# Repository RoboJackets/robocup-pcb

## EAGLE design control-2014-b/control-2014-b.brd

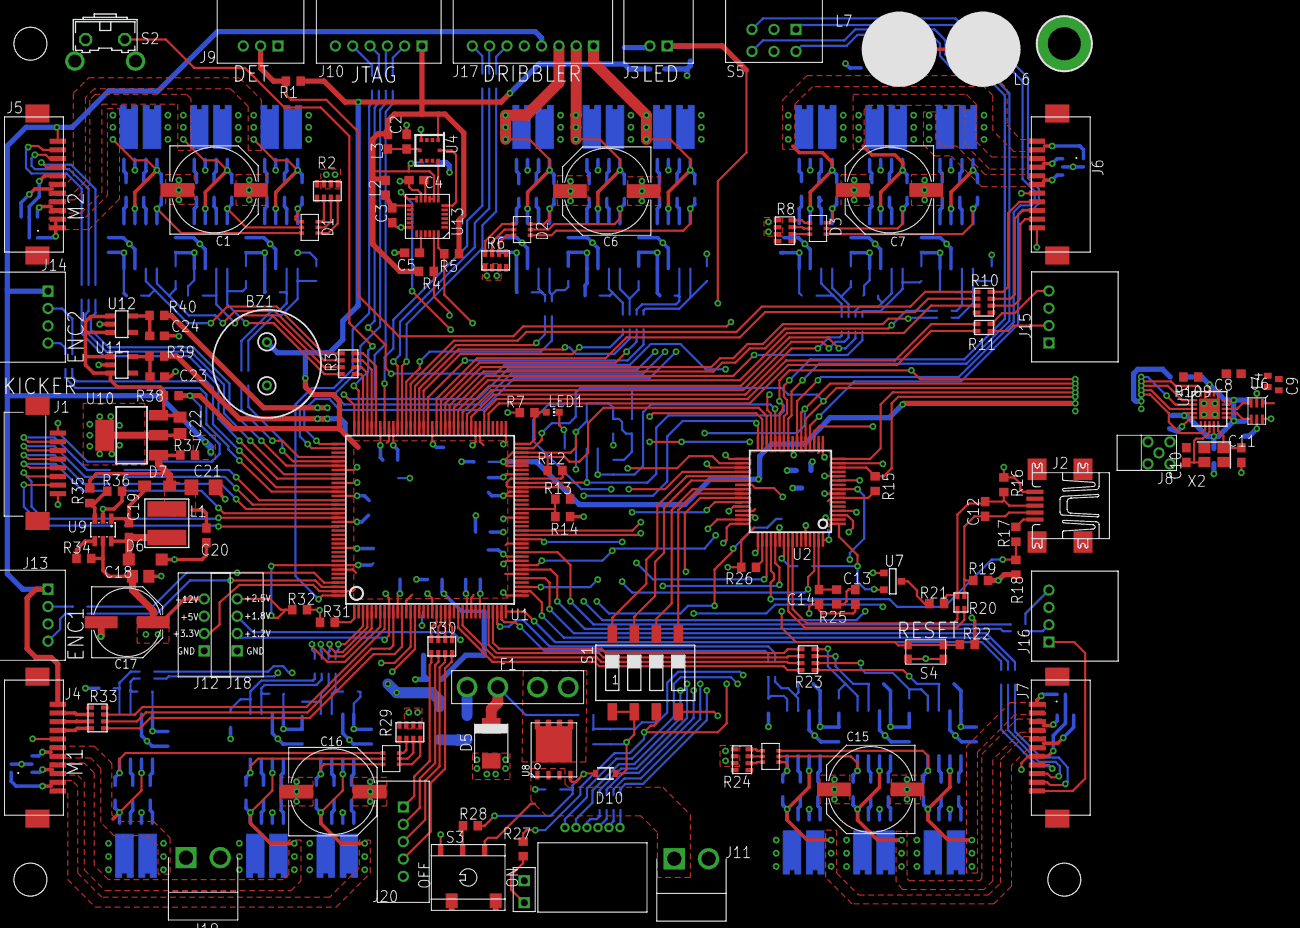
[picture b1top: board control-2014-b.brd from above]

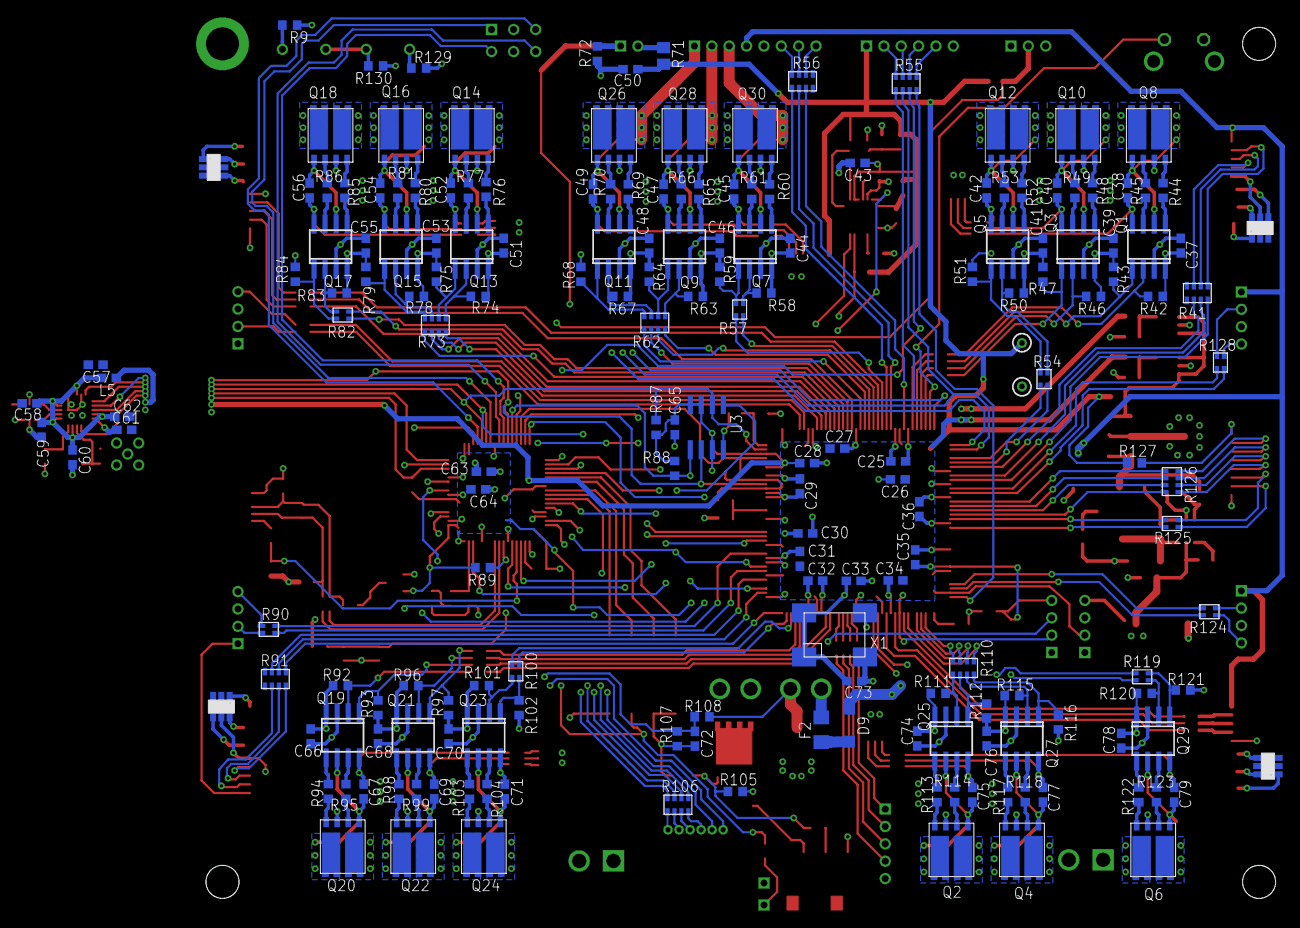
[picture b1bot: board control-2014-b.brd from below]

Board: 4 copper layers, 307 parts (184 on the bottom side), 336 nets.

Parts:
BZ1: PS12
C1, C6, C7, C15, C16: 470uF 25V; PANASONIC_G
C2, C3, C4, C20, C25, C26, C27, C28, C29, C30, C31, C32, C33, C34, C35, C36, C37, C39, C41, C43, C44, C46, C48, C51, C53, C55, C58, C61, C63, C64, C65, C66, C68, C70, C72, C73, C74, C76, C78: 100nF; C0603
C5, C59: 2.2nF; C0603
C8: 100pF; C0603
C9: 500R07S1R8BV4T; C0402
C10, C11: 27pF; C0603
C12: 33pF; C0603
C13, C19, C60, C62: 10nF; C0603
C14: 1nF; C0603
C17: 100uF 25V; PANASONIC_E
C18: 1uF 35V; C0805
C21: 22uF 6.3V; C1206
C22: 10uF; C0805
C23, C24, C50: 1uF; C0603
C38, C40, C42, C45, C47, C49, C52, C54, C56, C67, C69, C71, C75, C77, C79: 47nF; C0603
C57: 220nF; C0603
D1, D2, D3, D4, D8: MMBD4448HTW
D5: SMBJP6KE18A-TP; SMBJ
D6, D9: MBRX160-TP; SOD123
D7: BAS16H; SOD323-W
D10: CDSOD323-T15SC; SOD-323
F1: 2x BK6011 [30A]; FUSE_MINI_ATC
F2: SF-1206F100-2; F1206
H1: MOUNTING_HOLE
J1: 0528520870
J2: MINI-USB; UX60A-MB-5ST
J3: 2MM-2H; 2MM-2-H
J4, J5, J6, J7: Molex 0522711179; FH_11_HOR
J8: MMCX_RA
J9: 2MM-3H; 2MM-3-H
J10: 2MM-6H; 2MM-6-H
J11: BATT; JST_VH_2_RA
J12, J18: 2MM-4V; 2MM-4-V
J13, J14, J15, J16: 2MM-4H; 2MM-4-H
J17: 2MM-8H; 2MM-8-H
J19: JST_VH_2; JST_VH_2_RA
J20: 2MM-5V; 2MM-5-V
L1: SDR0403-270KL; SDR0403
L2, L3, L5: HZ0603B102R-10; C0603
L4: L-07C5N6SV6T; R0402
L6, L7: RL1014
LED1: CHIP-LED0603
LED2: LED2; 5350T5
LED3: LDS-M514RI-RA
Q1, Q3, Q5, Q7, Q9, Q11, Q13, Q15, Q17, Q19, Q21, Q23, Q25, Q27, Q29: FAN7380; SO08
Q2, Q4, Q6, Q8, Q10, Q12, Q14, Q16, Q18, Q20, Q22, Q24, Q26, Q28, Q30: BSC072N03LD
R1: 5.6k; R0603
R2, R6, R8, R24, R29: 22; RA_4_1206
R3, R10, R23, R30, R33, R41, R55, R56, R62, R73, R91, R106, R110, R126: 220; RA_4_1206
R4, R5, R14, R15, R18, R22, R32, R34, R36, R42, R43, R46, R47, R50, R51, R58, R59, R63, R64, R67, R68, R74, R75, R78, R79, R83, R84, R87, R88, R92, R93, R96, R97, R101, R102, R107, R111, R112, R115, R116, R120, R121: 10.0k; R0603
R7, R17, R27, R31: 220; R0603
R9, R129, R130: 10K; R0603
R11, R54, R57, R82, R90, R100, R119, R124, R125, R128: 220; RA_2_0606
R12, R13, R26, R89: NP; R0603
R16, R19: 330k; R0603
R20: 27; RA_2_0606
R21, R25: 1.5k; R0603
R28: 10; R0603
R35: 52.3k; R0603
R37, R38, R39, R40, R127: 0; R0603
R44, R45, R48, R49, R52, R53, R60, R61, R65, R66, R69, R70, R76, R77, R80, R81, R85, R86, R94, R95, R98, R99, R103, R104, R113, R114, R117, R118, R122, R123: 22; R0603
R71: 150 1/8W; R0805
R72, R105: 100k; R0603
R108: 68k; R0603
R109: 56k; R0603
S1: SWS004; SMS-004
S2: B3F-31XX
S3: G3T12AP_SPDT; G3T12AP_SP
S4: KMR2
S5: 94HBB16RAT; HEX-RA-2C
U1: XC3S100E; TQFP144
U2: AT91SAM7S256; SQFP-S-10X10-64
U3: M25P10; SO08
U4: KXTF9-2050; KXTF9
U5: CC1101; QLP20
U6: 0896BM15A0001
U7: FDV304P; SOT-23
U8: SI7141DP; POWERPAK_SO-8
U9: LM2734; SOT23-6L
U10: MCP1824ST-3302E/DB; SOT223
U11: MCP1824T-1202E/OT; SOT23-5
U12: MCP1824T-2502E/OT; SOT23-5
U13: IMU3000
U$25, U$27, U$28, U$29: SMS05T1; SC-74
X1: 18.432MHz; XTAL_LCC
X2: 644-1055-1-ND; XTAL-3.2X2.5

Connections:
12V_LOGIC: C17.+, C18.1, D9.C, J12.4, R34.2, U9.5
+1.2V: C26.1, C27.1, C31.1, C34.1, J18.2, R39.1, U1.9, U1.45, U1.80, U1.115
+1.8V: C64.1, J18.3, U2.8, U2.12, U2.24, U2.54, U2.64
+2.5V: C25.1, C29.1, C32.1, C35.1, J18.4, R7.1, R32.1, R40.1, U1.30, U1.65, U1.102, U1.137
+3.3V: BZ1.2, C28.1, C30.1, C33.1, C36.1, C43.1, C50.1, C63.1, C65.1, C73.1, J10.1, J12.2, L2.1, L3.1, L5.1, R1.1, R4.2, R5.2, R12.2, R13.2, R15.2, R22.2, R26.2, R27.2, R38.2, R71.1, R87.2, R88.2, R89.2, R127.1, S1.3, U1.13, U1.28, U1.42, U1.49, U1.62, U1.64, U1.67, U1.68, U1.70, U1.79, U1.100, U1.121, U1.138, U1.143, U2.1, U2.7, U2.18, U2.45, U2.58, U2.59, U3.3, U3.7, U3.8, U4.1, U7.2, U13.8, U13.9, X1.1, X1.4
+5V: J4.11, J5.11, J6.11, J7.11, J12.3, J13.1, J14.1, J15.1, J16.1, J17.4, R37.2
+12V: C1.+, C6.+, C7.+, C15.+, C16.+, C37.1, C39.1, C41.1, C44.1, C46.1, C48.1, C51.1, C53.1, C55.1, C66.1, C68.1, C70.1, C74.1, C76.1, C78.1, D5.C, F1.3, F1.4, F2.1, J19.1, Q1.3, Q2.D1@1, Q2.D1@2, Q3.3, Q4.D1@1, Q4.D1@2, Q5.3, Q6.D1@1, Q6.D1@2, Q7.3, Q8.D1@1, Q8.D1@2, Q9.3, Q10.D1@1, Q10.D1@2, Q11.3, Q12.D1@1, Q12.D1@2, Q13.3, Q14.D1@1, Q14.D1@2, Q15.3, Q16.D1@1, Q16.D1@2, Q17.3, Q18.D1@1, Q18.D1@2, Q19.3, Q20.D1@1, Q20.D1@2, Q21.3, Q22.D1@1, Q22.D1@2, Q23.3, Q24.D1@1, Q24.D1@2, Q25.3, Q26.D1@1, Q26.D1@2, Q27.3, Q28.D1@1, Q28.D1@2, Q29.3, Q30.D1@1, Q30.D1@2, R2.4, R2.6, R2.8, R6.4, R6.6, R6.8, R8.4, R8.6, R8.8, R24.4, R24.6, R24.8, R29.4, R29.6, R29.8, R108.2
/CONNECT: U2.19, U7.3
ARM_TDI: U1.109, U2.33
ARM_TDO: R55.5, U2.49
BALL_DET: J9.2, R1.2, U2.3
BALL_LED: J3.1, R72.1, U2.44
BATT_SENSE: C72.1, R107.2, R108.1, U2.4
BUZZ: BZ1.1, U2.32
CHASSIS: H1.GND, L6.P$1, R9.1
DDM: R20.2, U2.56
DDP: R20.4, U2.57
DISCHARGE: S2.1, U1.107
DONE: LED1.A, R7.2, U1.72
DP1: S1.8, U2.37
DP2: S1.7, U2.38
DP4: S1.5, U2.41
FLASH_NCS: R88.1, U1.39, U2.28, U3.1
FPGA_NCS: R12.1, U1.69, U2.30
FPGA_SPARE_0: R30.2, U1.20
FPGA_SPARE_1: R30.4, U1.21
FPGA_SPARE_2: R30.6, U1.22
FPGA_SPARE_3: R30.8, U1.23
FPGA_TDI: R55.7, U1.144
FS0: U1.52, U2.31
FS1: U1.51, U2.29
GND: C1.-, C2.2, C3.2, C4.2, C5.2, C6.-, C7.-, C9.2, C10.2, C11.2, C13.2, C14.2, C15.-, C16.-, C17.-, C18.2, C20.2, C21.2, C22.2, C23.2, C24.2, C25.2, C26.2, C27.2, C28.2, C29.2, C30.2, C31.2, C32.2, C33.2, C34.2, C35.2, C36.2, C37.2, C39.2, C41.2, C43.2, C44.2, C46.2, C48.2, C50.2, C51.2, C53.2, C55.2, C57.2, C58.2, C59.2, C60.2, C61.2, C62.2, C63.2, C64.2, C65.2, C66.2, C68.2, C70.2, C72.2, C73.2, C74.2, C76.2, C78.2, D5.A, D6.A, D10.1, J1.8, J2.5, J4.7, J5.7, J6.7, J7.7, J8.P$2, J8.P$3, J8.P$4, J8.P$5, J9.1, J9.3, J10.6, J11.2, J12.1, J13.3, J14.3, J15.3, J16.3, J17.5, J18.1, J19.2, J20.5, LED1.C, LED2.CATHODE, Q1.4, Q2.S2, Q3.4, Q4.S2, Q5.4, Q6.S2, Q7.4, Q8.S2, Q9.4, Q10.S2, Q11.4, Q12.S2, Q13.4, Q14.S2, Q15.4, Q16.S2, Q17.4, Q18.S2, Q19.4, Q20.S2, Q21.4, Q22.S2, Q23.4, Q24.S2, Q25.4, Q26.S2, Q27.4, Q28.S2, Q29.4, Q30.S2, R9.2, R14.1, R16.1, R18.1, R19.1, R36.1, R42.1, R43.1, R46.1, R47.1, R50.1, R51.1, R58.1, R59.1, R63.1, R64.1, R67.1, R68.1, R72.2, R74.1, R75.1, R78.1, R79.1, R83.1, R84.1, R92.1, R93.1, R96.1, R97.1, R101.1, R102.1, R107.1, R109.1, R111.1, R112.1, R115.1, R116.1, R120.1, R121.1, R129.2, R130.1, S1.1, S1.2, S1.4, S2.2, S3.6, S4.1, S4.3, S5.C1, S5.C2, U1.11, U1.19, U1.27, U1.37, U1.46, U1.55, U1.60, U1.61, U1.73, U1.90, U1.99, U1.118, U1.127, U1.133, U2.2, U2.17, U2.46, U2.60, U3.4, U4.4, U5.16, U5.19, U5.DAP, U6.2, U6.5, U6.6, U9.2, U10.2, U10.4, U11.2, U12.2, U13.11, U13.18, U$25.2, U$25.5, U$27.2, U$27.5, U$28.2, U$28.5, U$29.2, U$29.5, X1.2
I2C_SCL: R4.1, U2.36, U13.23
I2C_SDA: R5.1, U2.43, U13.24
ID0: S5.1, U2.23
ID1: S5.2, U2.25
ID2: S5.4, U2.20
ID3: S5.8, U2.26
IMU_INT: U2.34, U13.12
KCHARGE: R126.2, U1.125
KCHIP: R125.3, U1.128
KDONE: R126.4, U1.124
KKICK: R125.1, U1.126
KSCL: R126.6, U1.123
KSDA: R126.8, U1.122
LED_AE: R106.8, U2.35
LED_AN1: LED3.1, U2.9
LED_AN2: LED3.2, U2.42
LED_BF: R106.6, U2.15
LED_CG: R106.4, U2.47
LED_DDP: R106.2, U2.48
M1A: C75.2, J4.1, J4.2, Q2.D2@1, Q2.D2@2, Q2.S1, Q25.6, U$25.1
M1A_H: R110.7, U1.3
M1A_L: R110.5, U1.4
M1B: C77.2, J4.3, J4.4, Q4.D2@1, Q4.D2@2, Q4.S1, Q27.6, U$25.6
M1B_H: R110.3, U1.5
M1B_L: R110.1, U1.7
M1C: C79.2, J4.5, J4.6, Q6.D2@1, Q6.D2@2, Q6.S1, Q29.6, U$25.4
M1C_H: R119.3, U1.14
M1C_L: R119.1, U1.15
M1ENC_A: R124.1, U1.141
M1ENC_B: R124.3, U1.142
M1HALL_A: R33.3, U1.10
M1HALL_B: R33.1, U1.12
M1HALL_C: R33.5, U1.8
M2: R13.1, R14.2, U1.57
M2A: C38.2, J5.1, J5.2, Q1.6, Q8.D2@1, Q8.D2@2, Q8.S1, U$27.1
M2A_H: R3.7, U1.103
M2A_L: R3.5, U1.104
M2B: C40.2, J5.3, J5.4, Q3.6, Q10.D2@1, Q10.D2@2, Q10.S1, U$27.6
M2B_H: R3.3, U1.105
M2B_L: R3.1, U1.106
M2C: C42.2, J5.5, J5.6, Q5.6, Q12.D2@1, Q12.D2@2, Q12.S1, U$27.4
M2C_H: R54.3, U1.112
M2C_L: R54.1, U1.113
M2ENC_A: R128.1, U1.119
M2ENC_B: R128.3, U1.120
M2HALL_A: R41.5, U1.116
M2HALL_B: R41.3, U1.114
M2HALL_C: R41.7, U1.117
M3A: C52.2, J6.1, J6.2, Q13.6, Q14.D2@1, Q14.D2@2, Q14.S1, U$28.1
M3A_H: R73.7, U1.81
M3A_L: R73.5, U1.82
M3B: C54.2, J6.3, J6.4, Q15.6, Q16.D2@1, Q16.D2@2, Q16.S1, U$28.6
M3B_H: R73.3, U1.83
M3B_L: R73.1, U1.85
M3C: C56.2, J6.5, J6.6, Q17.6, Q18.D2@1, Q18.D2@2, Q18.S1, U$28.4
M3C_H: R82.3, U1.86
M3C_L: R82.1, U1.87
M3ENC_A: R11.2, U1.77
M3ENC_B: R11.4, U1.78
M3HALL_A: R10.3, U1.89
M3HALL_B: R10.1, U1.95
M3HALL_C: R10.5, U1.84
M4A: C67.2, J7.1, J7.2, Q19.6, Q20.D2@1, Q20.D2@2, Q20.S1, U$29.1
M4A_H: R23.7, U1.25
M4A_L: R23.5, U1.26
M4B: C69.2, J7.3, J7.4, Q21.6, Q22.D2@1, Q22.D2@2, Q22.S1, U$29.6
M4B_H: R23.3, U1.32
M4B_L: R23.1, U1.33
M4C: C71.2, J7.5, J7.6, Q23.6, Q24.D2@1, Q24.D2@2, Q24.S1, U$29.4
M4C_H: R100.3, U1.34
M4C_L: R100.1, U1.35
M4ENC_A: R90.1, U1.43
M4ENC_B: R90.3, U1.47
M4HALL_A: R91.3, U1.38
M4HALL_B: R91.1, U1.36
M4HALL_C: R91.5, U1.41
M5A: C49.2, J17.1, Q11.6, Q26.D2@1, Q26.D2@2, Q26.S1
M5A_H: R62.3, U1.88
M5A_L: R62.1, U1.91
M5B: C47.2, J17.2, Q9.6, Q28.D2@1, Q28.D2@2, Q28.S1
M5B_H: R62.7, U1.92
M5B_L: R62.5, U1.93
M5C: C45.2, J17.3, Q7.6, Q30.D2@1, Q30.D2@2, Q30.S1
M5C_H: R57.3, U1.94
M5C_L: R57.1, U1.96
M5HALL_A: R56.1, U1.97
M5HALL_B: R56.3, U1.98
M5HALL_C: R56.5, U1.101
MCU_PROGB: R31.1, R32.2, U2.11
MISO: U1.63, U2.27, U3.2, U5.2
MOSI: U1.44, U2.22, U3.5, U5.20
unnamed: J13.4, R124.4
unnamed: J10.3, R55.4
unnamed: Q25.2, R110.8, R111.2
unnamed: J10.5, R55.8
unnamed: Q25.7, R114.1
unnamed: Q2.G1, R114.2
unnamed: Q25.5, R113.1
unnamed: LED3.6, R106.1
unnamed: LED3.5, R106.3
unnamed: LED3.4, R106.5
unnamed: C20.1, C21.1, D7.A, L1.2, R35.2, R37.1, U10.1
unnamed: LED3.3, R106.7
unnamed: LED2.ANODE, R27.1
unnamed: Q2.G2, R113.2
unnamed: Q25.1, R110.6, R112.2
unnamed: Q27.2, R110.4, R115.2
unnamed: Q27.7, R118.1
unnamed: Q4.G1, R118.2
unnamed: Q27.5, R117.1
unnamed: D8.A2, R29.5
unnamed: Q4.G2, R117.2
unnamed: Q27.1, R110.2, R116.2
unnamed: Q29.2, R119.4, R120.2
unnamed: Q29.7, R123.1
unnamed: Q6.G1, R123.2
unnamed: Q29.5, R122.1
unnamed: Q6.G2, R122.2
unnamed: Q29.1, R119.2, R121.2
unnamed: C75.1, D8.C1, Q25.8
unnamed: C77.1, D8.C2, Q27.8
unnamed: C79.1, D8.C3, Q29.8
unnamed: D8.A1, R29.7
unnamed: D8.A3, R29.3
unnamed: Q1.2, R3.8, R42.2
unnamed: Q1.7, R45.1
unnamed: D1.A2, R2.5
unnamed: Q8.G1, R45.2
unnamed: Q1.5, R44.1
unnamed: Q8.G2, R44.2
unnamed: Q1.1, R3.6, R43.2
unnamed: Q3.2, R3.4, R46.2
unnamed: Q3.7, R49.1
unnamed: Q10.G1, R49.2
unnamed: Q3.5, R48.1
unnamed: Q10.G2, R48.2
unnamed: Q3.1, R3.2, R47.2
unnamed: Q5.2, R50.2, R54.4
unnamed: Q5.7, R53.1
unnamed: Q12.G1, R53.2
unnamed: Q5.5, R52.1
unnamed: Q12.G2, R52.2
unnamed: Q5.1, R51.2, R54.2
unnamed: C38.1, D1.C1, Q1.8
unnamed: C40.1, D1.C2, Q3.8
unnamed: C42.1, D1.C3, Q5.8
unnamed: D1.A1, R2.7
unnamed: D1.A3, R2.3
unnamed: Q13.2, R73.8, R74.2
unnamed: Q13.7, R77.1
unnamed: D3.A2, R8.5
unnamed: C22.1, R38.1, U10.3, U11.1, U11.3, U12.1, U12.3
unnamed: Q14.G1, R77.2
unnamed: Q13.5, R76.1
unnamed: Q14.G2, R76.2
unnamed: J3.2, R71.2
unnamed: Q13.1, R73.6, R75.2
unnamed: Q15.2, R73.4, R78.2
unnamed: Q15.7, R81.1
unnamed: C19.2, D6.C, L1.1, U9.6
unnamed: J4.8, R33.2
unnamed: Q16.G1, R81.2
unnamed: J4.10, R33.6
unnamed: Q15.5, R80.1
unnamed: Q16.G2, R80.2
unnamed: J4.9, R33.4
unnamed: J5.8, R41.4
unnamed: J5.10, R41.8
unnamed: J5.9, R41.6
unnamed: J6.8, R10.2
unnamed: J6.10, R10.6
unnamed: J6.9, R10.4
unnamed: J7.8, R91.2
unnamed: J7.10, R91.6
unnamed: C2.1, L3.2, U4.5
unnamed: J7.9, R91.4
unnamed: J17.6, R56.2
unnamed: J17.7, R56.4
unnamed: J1.2, R126.7
unnamed: C23.1, R39.2, U11.5
unnamed: C24.1, R40.2, U12.5
unnamed: R26.1, U2.50
unnamed: C12.2, J2.2, R19.2, R20.1
unnamed: J17.8, R56.6
unnamed: F1.1, F1.2, U8.D@1, U8.D@2, U8.D@3, U8.D@4
unnamed: Q15.1, R73.2, R79.2
unnamed: Q17.2, R82.4, R83.2
unnamed: J1.3, R126.5
unnamed: J1.4, R126.3
unnamed: R34.1, U9.4
unnamed: Q17.7, R86.1
unnamed: U4.9, U13.7
unnamed: C19.1, D7.C, U9.1
unnamed: Q18.G1, R86.2
unnamed: J1.5, R126.1
unnamed: R35.1, R36.2, U9.3
unnamed: J10.4, R55.6
unnamed: R89.1, U2.55
unnamed: J10.2, R55.2
unnamed: C12.1, J2.3, R16.2, R20.3, R21.1
unnamed: R21.2, U7.1
unnamed: C13.1, R25.1
unnamed: C14.1, R25.2, U2.63
unnamed: Q17.5, R85.1
unnamed: D9.A, F2.2
unnamed: Q18.G2, R85.2
unnamed: Q17.1, R82.2, R84.2
unnamed: J13.2, R124.2
unnamed: J16.4, R90.4
unnamed: J16.2, R90.2
unnamed: J15.4, R11.3
unnamed: J15.2, R11.1
unnamed: J14.4, R128.4
unnamed: J14.2, R128.2
unnamed: C52.1, D3.C1, Q13.8
unnamed: U4.10, U13.6
unnamed: C3.1, L2.2, U13.13
unnamed: C4.1, U13.10
unnamed: C5.1, U13.20
unnamed: J1.6, R125.2
unnamed: J1.7, R125.4
unnamed: J1.1, R127.2
unnamed: C61.1, U5.5
unnamed: R109.2, U5.17
unnamed: C11.1, U5.10, X2.1
unnamed: J20.3, R30.5
unnamed: J20.2, R30.3
unnamed: J20.1, R30.1
unnamed: J20.4, R30.7
unnamed: C10.1, U5.8, X2.3
unnamed: C54.1, D3.C2, Q15.8
unnamed: L4.1, U6.1
unnamed: C56.1, D3.C3, Q17.8
unnamed: C8.1, C9.1, L4.2
unnamed: J2.1, R17.2
unnamed: U5.12, U6.4
unnamed: D3.A1, R8.7
unnamed: D3.A3, R8.3
unnamed: Q19.2, R23.8, R92.2
unnamed: Q19.7, R95.1
unnamed: D4.A2, R24.5
unnamed: Q20.G1, R95.2
unnamed: Q19.5, R94.1
unnamed: Q20.G2, R94.2
unnamed: Q19.1, R23.6, R93.2
unnamed: Q21.2, R23.4, R96.2
unnamed: Q21.7, R99.1
unnamed: Q22.G1, R99.2
unnamed: Q21.5, R98.1
unnamed: Q22.G2, R98.2
unnamed: Q21.1, R23.2, R97.2
unnamed: Q23.2, R100.4, R101.2
unnamed: Q23.7, R104.1
unnamed: Q24.G1, R104.2
unnamed: Q23.5, R103.1
unnamed: Q24.G2, R103.2
unnamed: Q23.1, R100.2, R102.2
unnamed: C67.1, D4.C1, Q19.8
unnamed: C69.1, D4.C2, Q21.8
unnamed: C71.1, D4.C3, Q23.8
unnamed: D4.A1, R24.7
unnamed: D4.A3, R24.3
unnamed: U5.13, U6.3
unnamed: C8.2, J8.P$1
unnamed: Q11.2, R62.4, R67.2
unnamed: Q11.7, R70.1
unnamed: D2.A2, R6.5
unnamed: Q26.G1, R70.2
unnamed: Q11.5, R69.1
unnamed: Q26.G2, R69.2
unnamed: Q11.1, R62.2, R68.2
unnamed: Q9.2, R62.8, R63.2
unnamed: Q9.7, R66.1
unnamed: Q28.G1, R66.2
unnamed: Q9.5, R65.1
unnamed: Q28.G2, R65.2
unnamed: Q9.1, R62.6, R64.2
unnamed: Q7.2, R57.4, R58.2
unnamed: Q7.7, R61.1
unnamed: Q30.G1, R61.2
unnamed: Q7.5, R60.1
unnamed: Q30.G2, R60.2
unnamed: Q7.1, R57.2, R59.2
unnamed: C49.1, D2.C3, Q11.8
unnamed: C47.1, D2.C2, Q9.8
unnamed: C45.1, D2.C1, Q7.8
unnamed: D2.A1, R6.7
unnamed: D2.A3, R6.3
unnamed: R28.1, S3.5
unnamed: D10.2, R28.2, R105.1, U8.4
unnamed: L6.P$2, L7.P$1, R130.2
unnamed: L7.P$2, R129.1
PROGB: R31.2, U1.1
RADIO_INT: U2.16, U5.3
RADIO_NCS: R15.1, U2.14, U5.7
RADIO_VDD: C57.1, C58.1, C59.1, C60.1, C62.1, L5.2, U5.4, U5.9, U5.11, U5.14, U5.15, U5.18
SCK: R87.1, U1.71, U2.21, U3.6, U5.1
SRST: R22.1, S4.2, S4.4, U2.39
SYSCLK: U1.50, U2.62, X1.3
TCK: R55.3, U1.110, U2.53
TMS: R55.1, U1.108, U2.51
TST: S1.6, U2.40
VBATT: J11.1, R105.2, S3.4, U8.S@1, U8.S@2, U8.S@3
VBUS: R17.1, R18.2, U2.52

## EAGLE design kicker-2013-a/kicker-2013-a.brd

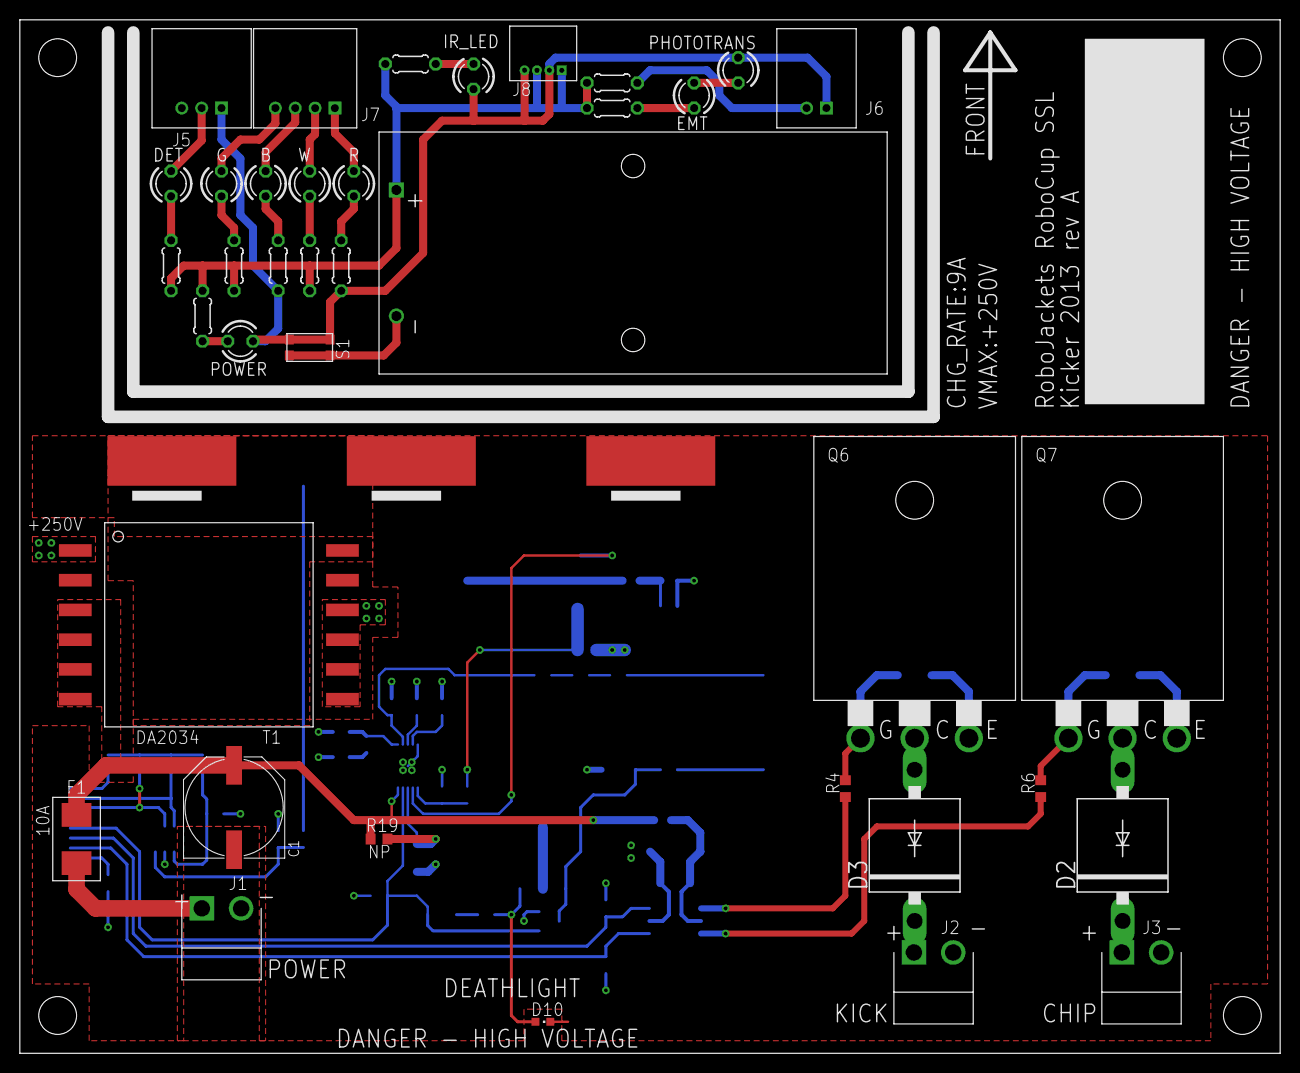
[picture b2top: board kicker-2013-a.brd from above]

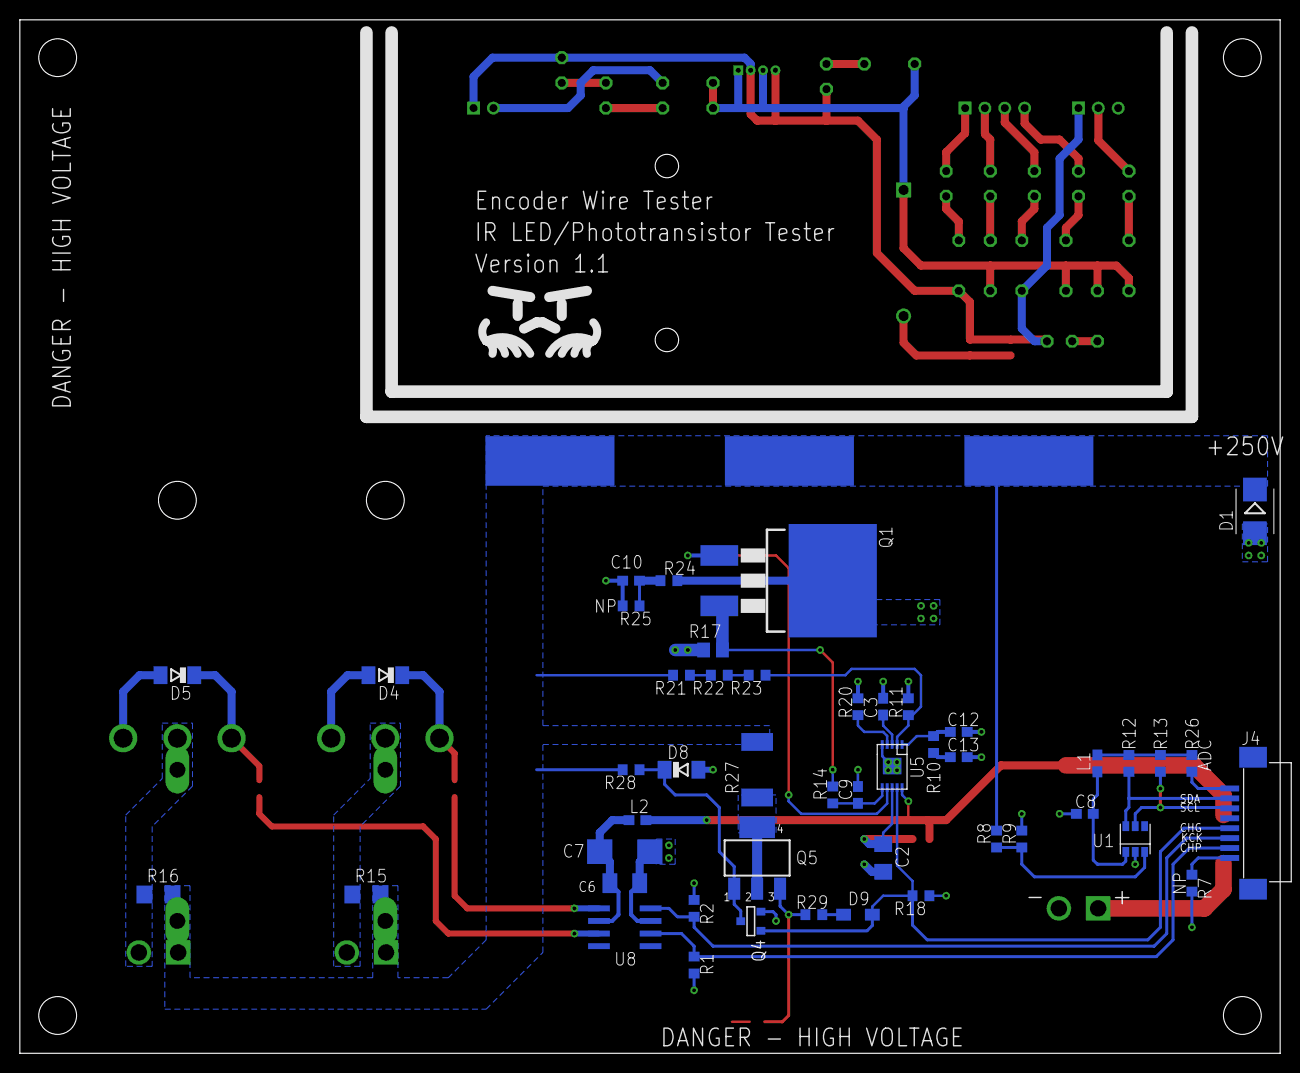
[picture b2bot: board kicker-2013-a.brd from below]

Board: 2 copper layers, 127.0 x 104.1 mm, 88 parts (47 on the bottom side), 57 nets.

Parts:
B: LED3MM
C1: UWT1E471MNL1GS; PANASONIC_G
C2: 4.7uF, 25v; C1206
C3, C8: 100nF; C0603
C6: 4.7uF; C1206K
C7: 47uF; C/6032-28R
C9, C13: 22nF; C0603
C10: 220pF 100V; C0603
C12: 100pF; C0603
D1: STTH3R06U; SMB
D2, D3: 6A6-T; P6-15
D4, D5, D8: BZV55-B18,115; SOD80C
D9: BAS16H; SOD323-W
D10: LTST-S270KRKT; CHIPLED_0603
DET: LED3MM
EMT: LED3MM
F1: 10A; NANO2_157
G: LED3MM
IR_LED: LED3MM
J1: POWER; JST_VH_2_RA
J2: KICK; JST_VH_2_RA
J3: CHIP; JST_VH_2_RA
J4: 0528520870
J5: 2MM-3H; 2MM-3-H
J6: 2MM-2H; 2MM-2-H
J7: 2MM-4H; 2MM-4-H
J8: 1.25MM-4H; 1.25MM-4-H
L1, L2: HZ0603B102R-10; C0603
PHOTOTRANS: TLLG4400; LED3MM
POWER: LED3MM
Q1: STB40NF20; D2PACK
Q4: FDV303N; SOT-23
Q5: FQT1N80; SOT223
Q6, Q7: IXGK400N30A3; TO264
R: LED3MM
R1, R2, R9, R12, R13, R18: 10.0k; R0603
R3, R5, R30, R31, R32, R33, R35, R36, R37: 0204/5
R4, R6: 10; R0603
R7, R19, R25, R26: NP; R0603
R8: 1.00M; R0603
R10: 6.8k; R0603
R11: 16.20k, 1% (MCR03EZPFX1622); R0603
R14, R24: 22; R0603
R15, R16: 680K; R1206
R17: 0.015 (ERJ-6BWFR015V); R0805
R20: 140k; R0603
R21: 470k 1%; R0603
R22, R23: 1.00M, 1% (MCR03EZPFX1004); R0603
R27: RHC2512FT33K0; R2512
R28: 10M; R0603
R29: 220; R0603
S1: KMR2
T1: DA2034
U1: ADC081C027; SOT23-6
U5: LT3757; MSOP-10-MSE
U8: TC4427; SO08
U$1: BATT-AAA-2
U$3, U$4, U$5: EET-UQ2E821CA; 22CAP
W: LED3MM

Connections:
+3V3: L1.1, R12.2, R13.2, R26.2
+12V: C1.+, F1.P$2, L2.2, R19.1, T1.3, T1.4, T1.5, T1.6, U5.10
CHARGE: D9.A, J4.4, Q4.3, R18.2, U5.9
CHIP: J4.2, R1.2, U8.2
GND: C1.-, C2.2, C3.2, C6.2, C7.-, C8.2, C9.2, C10.2, C12.2, C13.2, D4.A, D5.A, D8.A, D10.C, J1.2, Q4.2, Q6.E, Q7.E, R1.1, R2.1, R7.2, R9.1, R11.1, R17.1, R18.1, R20.2, R25.1, T1.12, U1.2, U5.5, U5.11, U8.3, U$3.2, U$4.2, U$5.2
GND1: S1.1, S1.3, U$1.GND
GND2: IR_LED.K, J5.1, J6.1, J8.2, J8.4, PHOTOTRANS.A, POWER.K, R30.2, R32.2, S1.2, S1.4
HV: D1.C, D2.C, D3.C, J2.1, J3.1, R8.2, R15.2, R16.2, R21.2, R27.2, R28.2, U$3.1, U$4.1, U$5.1
KICK: J4.3, R2.2, U8.4
unnamed: D5.C, Q7.G, R6.2
unnamed: Q1.1, U5.7
unnamed: J4.1, R7.1
unnamed: C12.1, R10.1, U5.1
unnamed: C13.1, R10.2
unnamed: POWER.A, R3.1
unnamed: R22.1, R23.2
unnamed: D4.C, Q6.G, R4.2
unnamed: R8.1, R9.2, U1.3
unnamed: DET.A, R36.1
unnamed: D2.A, J3.2, Q7.C, R16.1
unnamed: IR_LED.A, R33.1
unnamed: J4.8, R26.1
unnamed: R4.1, U8.5
unnamed: R6.1, U8.7
unnamed: D3.A, J2.2, Q6.C, R15.1
unnamed: DET.K, J5.2
unnamed: C6.1, C7.+, L2.1, U8.6
unnamed: C8.1, L1.2, U1.1
unnamed: D8.C, Q4.1, Q5.1, R28.1
unnamed: Q5.2, Q5.4, R27.1
unnamed: R21.1, R22.2
unnamed: R11.2, R23.1, U5.2
unnamed: F1.P$1, J1.1
unnamed: EMT.K, PHOTOTRANS.K
unnamed: C3.1, U5.3
unnamed: R20.1, U5.4
unnamed: C2.1, R19.2, U5.8
unnamed: D10.A, Q5.3, R29.2
unnamed: C9.1, R14.1, U5.6
unnamed: C10.1, R24.1, R25.2
unnamed: D9.C, R29.1
unnamed: G.A, R5.1
unnamed: B.K, R30.1
unnamed: R31.1, W.A
unnamed: R.K, R32.1
unnamed: EMT.A, R35.1
unnamed: J6.2, R37.1
unnamed: G.K, J7.4
unnamed: B.A, J7.3
unnamed: J7.2, W.K
unnamed: J7.1, R.A
unnamed: Q1.2, R24.2, T1.7, T1.8, T1.9, T1.10
unnamed: D1.A, T1.1
NAG: Q1.3, R14.2, R17.2
SCL: J4.6, R13.1, U1.5
SDA: J4.7, R12.1, U1.6
V+: J8.1, J8.3, R3.2, R5.2, R31.2, R33.2, R35.2, R36.2, R37.2, U$1.V+

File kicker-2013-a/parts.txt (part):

Partlist

Exported from kicker.brd at 3/17/2013 1:23:56 PM

EAGLE Version 6.4.0 Copyright (c) 1988-2013 CadSoft

Assembly variant: 

Part     Value                       Package      Library        Position (inch)       Orientation

C1       UWT1E471MNL1GS              PANASONIC_G  rcl            (0.7 0.825)           R90
C2       4.7uF, 25v                  C1206        rcl            (1.425 0.625)         MR270
C3       100nF                       C0603        rcl            (1.425 1.225)         MR90
C6       4.7uF                       C1206K       rcl            (2.45 0.525)          MR0
C7       47uF                        C/6032-28R   rcl            (2.45 0.65)           MR180
C8       100nF                       C0603        rcl            (0.625 0.8)           MR180
C9       22nF                        C0603        rcl            (1.525 0.875)         MR90
C10      220pF 100V                  C0603        rcl            (2.425 1.725)         MR180
C12      100pF                       C0603        rcl            (1.225 1.225)         MR90
C13      22nF                        C0603        rcl            (1.125 1.225)         MR90
D1       STTH3R06U                   SMB          diode          (-0.05 2)             MR270
D2       6A6-T                       P6-15        diode          (4.225 0.675)         R90
D3       6A6-T                       P6-15        diode          (3.4 0.675)           R90
D4       BZV55-B18,115               SOD80C       diode          (3.4 1.35)            MR180
D5       BZV55-B18,115               SOD80C       diode          (4.225 1.35)          MR180
D8       BZV55-B18,115               SOD80C       diode          (2.225 0.975)         MR0
D9       BAS16H                      SOD323-W     diode          (1.525 0.4)           MR0
D10      LTST-S270KRKT               CHIPLED_0603 led            (1.925 -0.025)        R270
F1       10A                         NANO2_157    littlefuse     (0.075 0.7)           R90
J1       POWER                       JST_VH_2_RA  jst_vh         (0.65 0.425)          R0
J2       KICK                        JST_VH_2_RA  jst_vh         (3.475 0.25)          R0
J3       CHIP                        JST_VH_2_RA  jst_vh         (4.3 0.25)            R0
J4       0528520870                  0528520870   con-robocup    (0.05 0.625)          MR90
J5       2MM-3H                      2MM-3-H      2mm            (0.475 3.6)           R0
J6       2MM-2H                      2MM-2-H      2mm            (3 3.6)               R0
J7       2MM-4H                      2MM-4-H      2mm            (0.95 3.6)            R0
J8       1.25MM-4H                   1.25MM-4-H   1.25mm         (1.825 3.75)          MR0
L1       HZ0603B102R-10              C0603        radio          (0.575 1)             MR270
L2       HZ0603B102R-10              C0603        radio          (2.4 0.775)           MR0
LED1                                 LED3MM       led            (0.45 2.55)           R0
LED2                                 LED3MM       led            (0.575 3.3)           R90
LED3                                 LED3MM       led            (0.75 3.3)            R270
LED4                                 LED3MM       led            (0.925 3.3)           R90
LED5                                 LED3MM       led            (1.1 3.3)             R270
LED6                                 LED3MM       led            (1.65 3.7)            R90
LED7                                 LED3MM       led            (0.375 3.3)           R90
LED8                                 LED3MM       led            (2.65 3.55)           R90
Q1       STB40NF20                   D2PACK       fairchild      (1.725 1.725)         MR270
Q4       FDV303N                     SOT-23       zetex          (1.95 0.375)          MR270
Q5       FQT1N80                     SOT223       zetex          (1.925 0.625)         MR0
Q6       IXGK400N30A3                TO264        IXYS           (3.4 1.35)            R0
Q7       IXGK400N30A3                TO264        IXYS           (4.225 1.35)          R0
Q99      TLLG4400                    LED3MM       led            (2.65 3.8)            R90
R1       10.0k                       R0603        rcl            (2.175 0.2)           MR90
R2       10.0k                       R0603        rcl            (2.175 0.425)         MR270
R3                                   0204/5       resistor       (0.3 2.65)            R90
R4       10                          R0603        rcl            (3.125 0.9)           R90
R5                                   0204/5       resistor       (0.575 2.975)         R270
R6       10                          R0603        rcl            (3.9 0.9)             R90
R7       NP                          R0603        rcl            (0.2 0.525)           MR270
R8       1.00M                       R0603        rcl            (0.975 0.7)           MR90
R9       10.0k                       R0603        rcl            (0.875 0.7)           MR270
R10      6.8k                        R0603        rcl            (1.175 1.125)         MR0
R11      16.20k, 1% (MCR03EZPFX1622) R0603        rcl            (1.325 1.225)         MR270
R12      10.0k                       R0603        rcl            (0.45 1)              MR90
R13      10.0k                       R0603        rcl            (0.325 1)             MR90
R14      22                          R0603        rcl            (1.625 0.875)         MR90
R15      680K                        R1206        rcl            (3.475 0.48)          MR0
R16      680K                        R1206        rcl            (4.3 0.48)            MR0
R17      0.015 (ERJ-6BWFR015V)       R0805        rcl            (2.1 1.45)            MR0
R18      10.0k                       R0603        rcl            (1.275 0.475)         MR180
R19      NP                          R0603        rcl            (1.275 0.7)           R0
R20      140k                        R0603        rcl            (1.525 1.225)         MR90
R21      470k 1%                     R0603        rcl            (2.225 1.35)          MR180
R22      1.00M, 1% (MCR03EZPFX1004)  R0603        rcl            (2.075 1.35)          MR180
R23      1.00M, 1% (MCR03EZPFX1004)  R0603        rcl            (1.925 1.35)          MR180
R24      22                          R0603        rcl            (2.275 1.725)         MR0
R25      NP                          R0603        rcl            (2.425 1.625)         MR0
R26      NP                          R0603        rcl            (0.2 1)               MR90
R27      RHC2512FT33K0               R2512        rcl            (1.925 0.975)         MR90
R28      10M                         R0603        rcl            (2.425 0.975)         MR180
R29      220                         R0603        rcl            (1.7 0.4)             MR180
R30                                  0204/5       resistor       (0.75 2.975)          R270
R31                                  0204/5       resistor       (0.925 2.975)         R270
R32                                  0204/5       resistor       (1.1 2.975)           R270
R33                                  0204/5       resistor       (1.55 3.55)           R180
R34                                  0204/5       resistor       (1.55 3.45)           R0
R35                                  0204/5       resistor       (2.425 3.5)           R180
R36                                  0204/5       resistor       (0.375 2.975)         R270
R37                                  0204/5       resistor       (2.15 3.675)          R180
R38                                  0204/5       resistor       (2.425 3.675)         R180
S1       KMR2                        KMR2         switch-robocup (0.925 2.7)           R180
T1       DA2034                      DA2034       coilcraft      (0.6 1.55)            R180
U$1      BATT-AAA-2                  BATT-AAA-2   battholders    (1.3 2.875)           R270
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
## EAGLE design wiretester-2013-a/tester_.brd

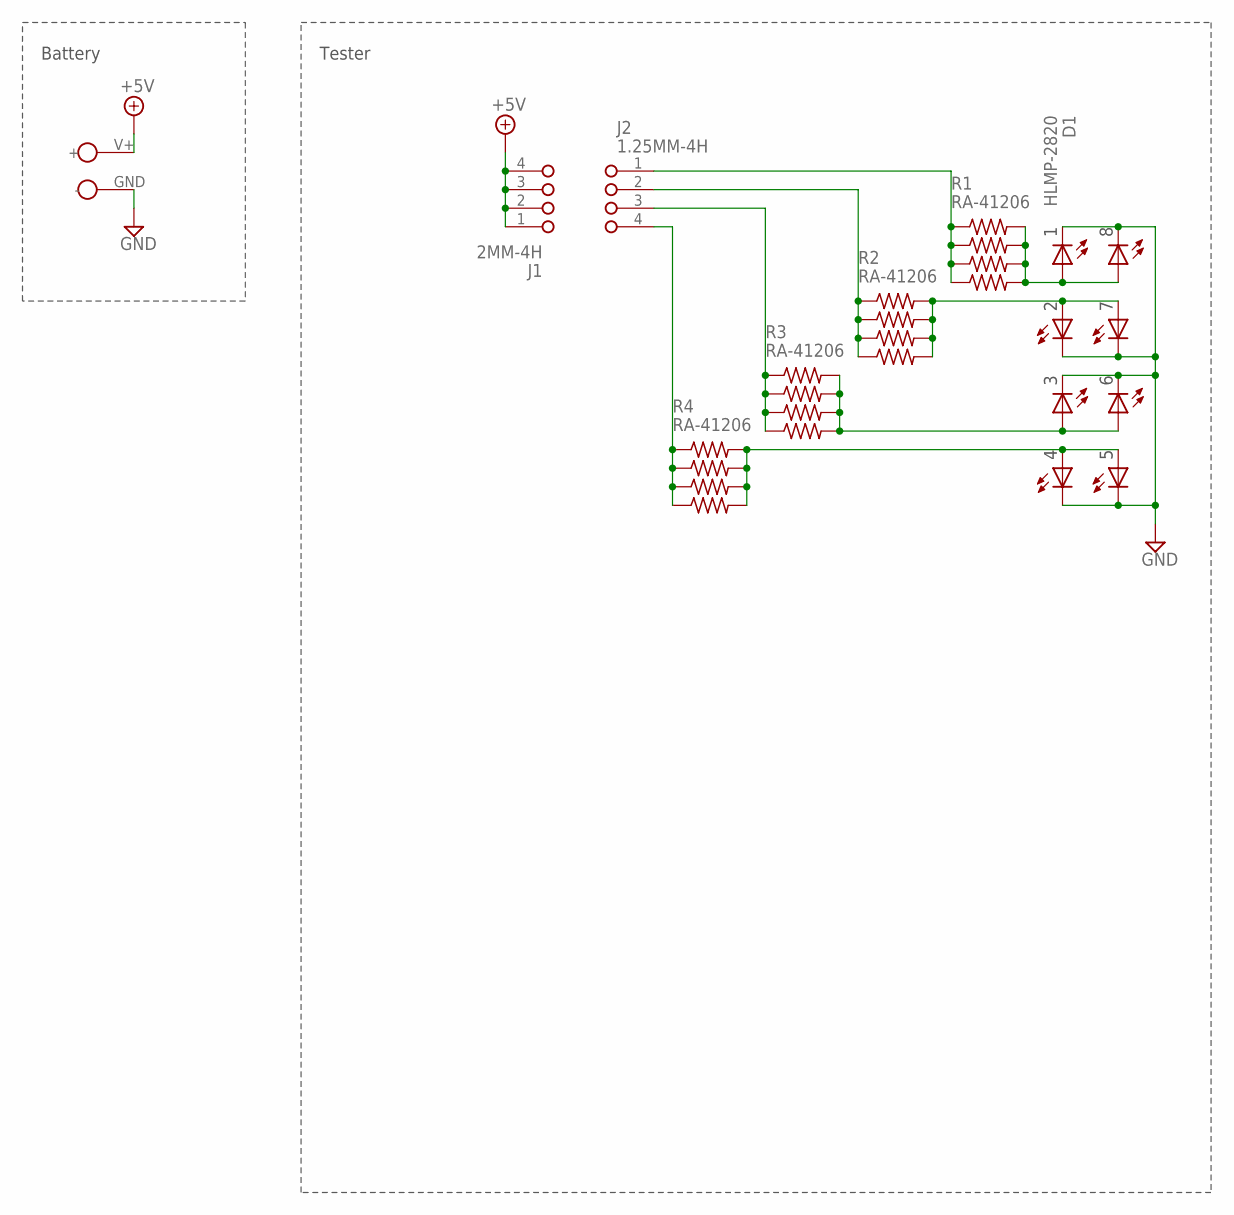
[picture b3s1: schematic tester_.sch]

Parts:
D1: HLMP-2820
J1: 2MM-4H; 2MM-4-H
J2: 1.25MM-4H; 1.25MM-4-H
R1, R2, R3, R4: RA-41206; RA_4_1206
U$1: BATT-AAA-2

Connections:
+5V: J1.1, J1.2, J1.3, J1.4, U$1.V+ (+)
GND: D1.1, D1.4, D1.5, D1.8, D1.9, D1.12, D1.13, D1.16, U$1.GND (-)
unnamed: J2.1, R1.1, R1.3, R1.5, R1.7
unnamed: J2.2, R2.1, R2.3, R2.5, R2.7
unnamed: J2.3, R3.1, R3.3, R3.5, R3.7
unnamed: J2.4, R4.1, R4.3, R4.5, R4.7
unnamed: D1.3, D1.14, R2.2, R2.4, R2.6, R2.8
unnamed: D1.2, D1.15, R1.2, R1.4, R1.6, R1.8
unnamed: D1.7, D1.10, R4.2, R4.4, R4.6, R4.8
unnamed: D1.6, D1.11, R3.2, R3.4, R3.6, R3.8

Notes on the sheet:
Tester
Battery

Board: 2 copper layers, 8 parts (0 on the bottom side), 10 nets, no tracks yet.
